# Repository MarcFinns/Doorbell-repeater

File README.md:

# Doorbell Repeater

Can be invoked via HTTTP from any home automation system
- Works with any I2S dac (tested with Adafruit MAX98357 board)
- Plays an MP3 file when **/ring** endpoint is invoked
- reboots via **/reboot** endpoint
- MP3 file can be uploaded via **/upload** endpoint
- Status can be visualised via **/settings** endpoing
- Integrates WifiManager for network selection
- Integrates ArduinoOTA for updates without cable

  **NOTE:** better compiled with Arduino 1.x IDE as more heap is available

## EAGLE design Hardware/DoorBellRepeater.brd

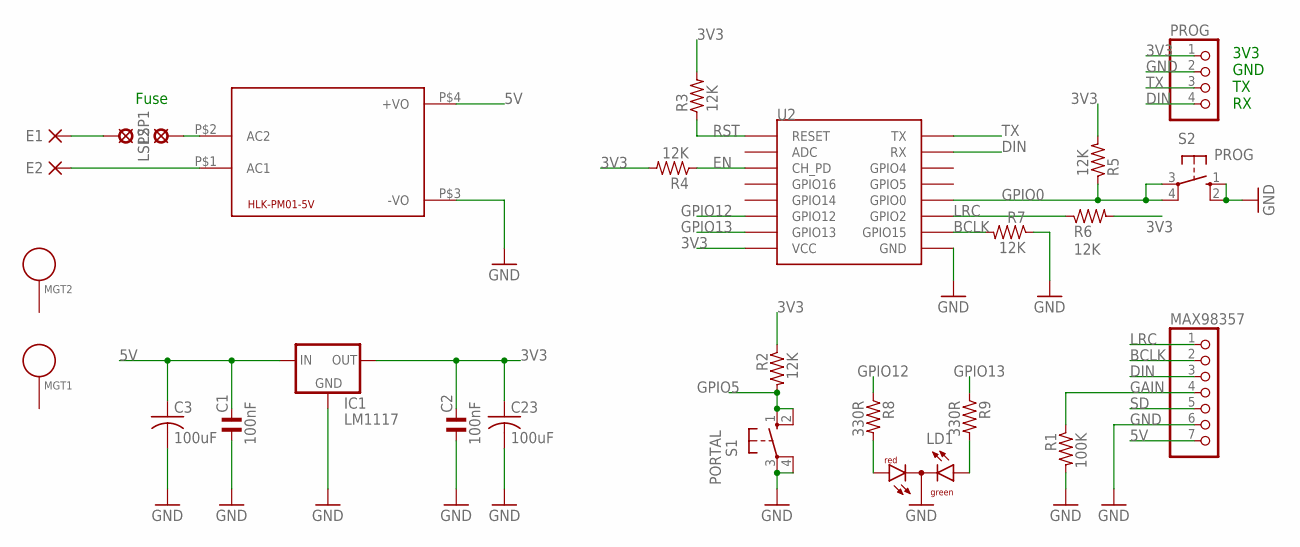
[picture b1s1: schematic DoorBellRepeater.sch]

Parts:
C1, C2: 100nF; C0805MP
C3, C23: 100uF; C0805K
E1, E2: PAD-0460S-S; 0460S-S
HLK-PM01-5V: HLK-PM013W; HLK-PM01
IC1: LM1117; SOT223
LD1: DUOLED-RG-C; DUOLED-C-5MM
LSP1, LSP2: LSP10
MAX98357: PINHD-1X7; 1X07
MGT1, MGT2: MOUNTING_HOLE; BEAGLEBONEBLACK_MOUNTING_HOLE
PROG: PINHD-1X4; 1X04
R1: 100K; 0805_RES
R2, R3, R4, R5, R6, R7: 12K; 0805_RES
R8, R9: 330R; 0805_RES
S1: PORTAL; B3F-10XX
S2: PROG; B3F-10XX
U2: ESP12

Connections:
3V3: C2.2, C23.1, IC1.2 (OUT), PROG.1, R2.1, R3.2, R4.2, R5.2, R6.2, U2.VCC
5V: C1.2, C3.1, HLK-PM01-5V.P$4 (+VO), IC1.3 (IN), MAX98357.7
BCLK: MAX98357.2, R7.2, U2.GPIO15
DIN: MAX98357.3, PROG.4, U2.RX
EN: R4.1, U2.CH_PD
GAIN: MAX98357.4, R1.1
GND: C1.1, C2.1, C3.2, C23.2, HLK-PM01-5V.P$3 (-VO), IC1.1 (GND), LD1.C, MAX98357.6, PROG.2, R1.2, R7.1, S1.3, S1.4 (P1), S2.1 (S), S2.2 (S1), U2.GND
GPIO0: R5.1, S2.3, S2.4 (P1), U2.GPIO0
GPIO5: R2.2, S1.1 (S), S1.2 (S1)
GPIO12: R8.1, U2.GPIO12
GPIO13: R9.1, U2.GPIO13
LRC: MAX98357.1, R6.1, U2.GPIO2
unnamed: E2.1, HLK-PM01-5V.P$1 (AC1)
unnamed: HLK-PM01-5V.P$2 (AC2), LSP1.MP
unnamed: LD1.AR, R8.2
unnamed: LD1.AX (AG), R9.2
unnamed: E1.1, LSP2.MP
RST: R3.1, U2.RESET
SD: MAX98357.5
TX: PROG.3, U2.TX

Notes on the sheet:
3V3 GND TX RX
Fuse

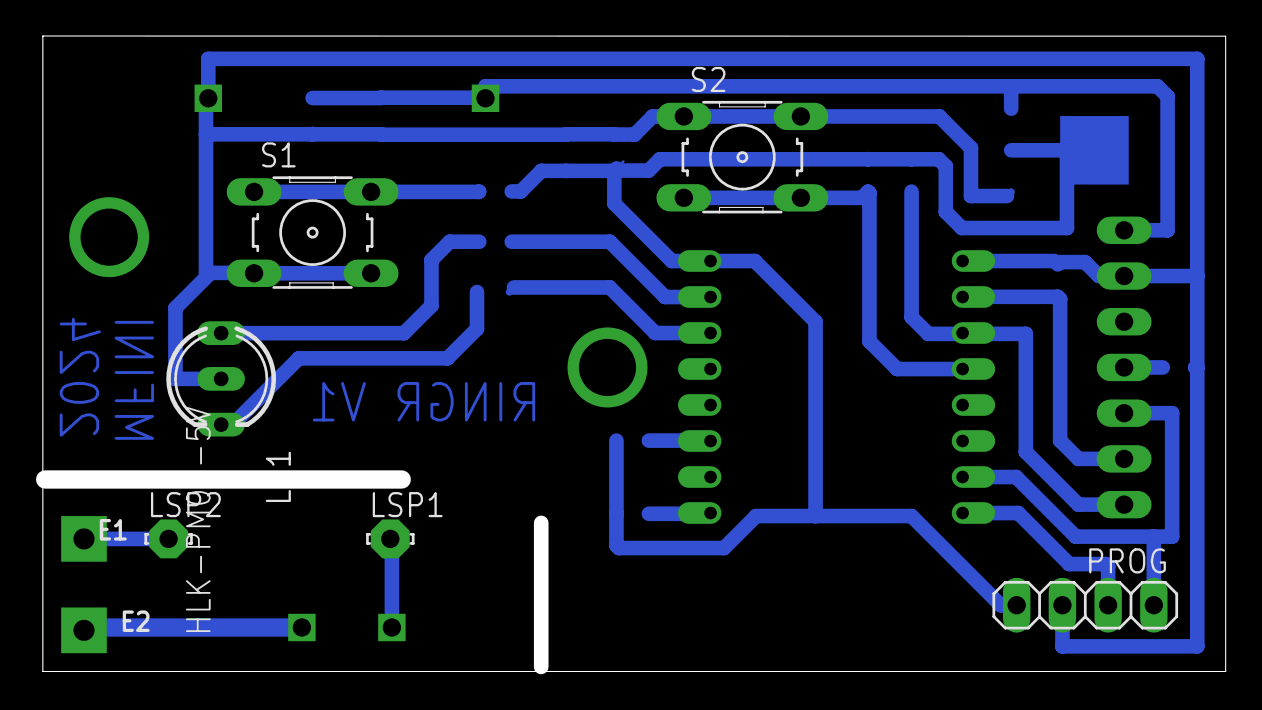
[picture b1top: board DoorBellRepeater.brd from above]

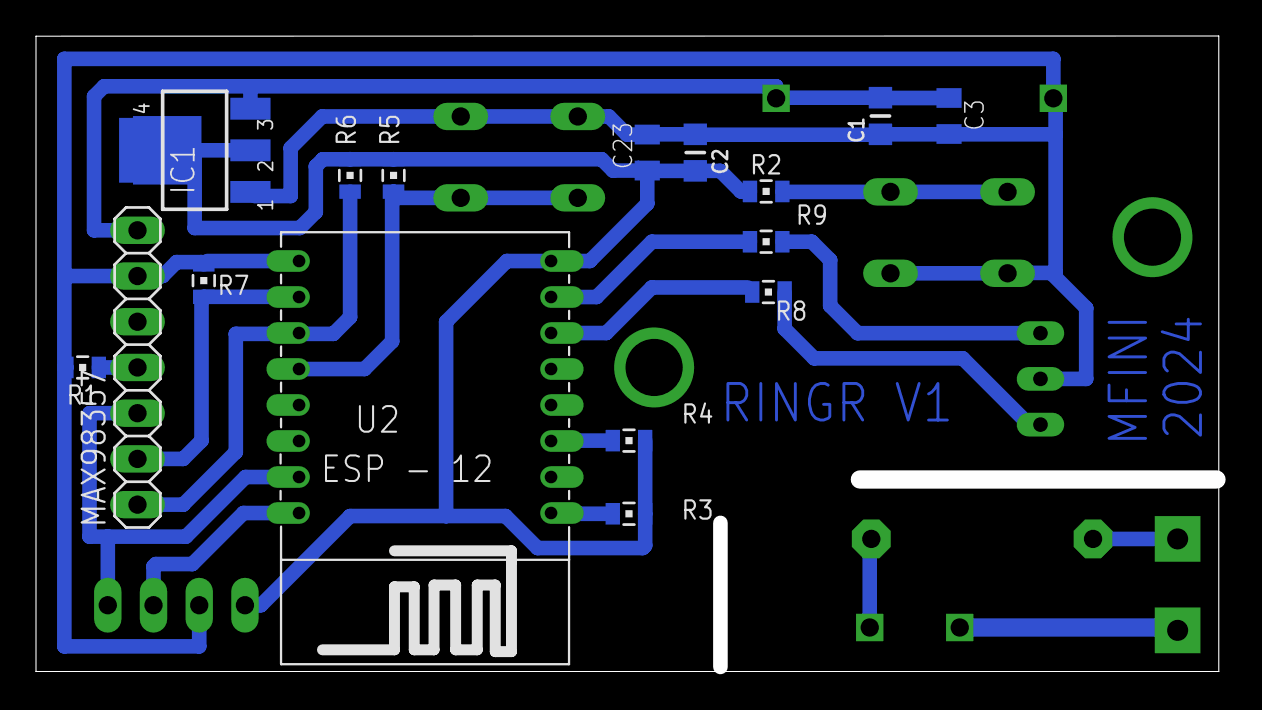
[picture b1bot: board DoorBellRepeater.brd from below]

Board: 2 copper layers, 65.1 x 34.4 mm, 27 parts (16 on the bottom side), 19 nets.

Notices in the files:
parts and their libraries:
rc-master-smd: Copyright (C) 2007-2008, Bob Starr
dpads: Copyright (C) 2008, Bob Starr
SparkFun-Aesthetics: Licensing: Creative Commons ShareAlike 4.0 International - https://creativecommons.org/licenses/by-sa/4.0
